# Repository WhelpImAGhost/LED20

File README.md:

# ECE 411 - LED20
### Team 1
- Brad Glaubitz
- Chris Kane-Pardy
- Caleb Monti
- Henry Sanders

## Project Overview
The purpose of the LED20 project is to add a fun and interesting spin to modern D20s (20 sided dice) for various tabletop games. Rather than a standard D20 which simply shows which face is rolled, the LED20 will illuminate the face that was rolled, and play special sound effects when a 1 or 20 is rolled. This added flare will spice up any tabletop game, and can be customized to your liking! [^1]

## Important Files and Folders Directory
This repository holds all design and development documents that were either assigned or created out of necessity throughout this project, including the Product Design Specification and Bill of Materials. However, for someone interested in creating their own copy of the LED20, some of these files and folders are not required. So, we have compiled a list of the files and folders that are necessary for understanding and replicating this project

### Links to files and folders
- [Full Project Description](./Project%20Info%20and%20Requirements/Project%20Information%20and%20Requirements.pdf): A more in-depth explanation of the project details and required features
- [Functional Decomposition](./Functional%20Decomposition/): Other high-detail files which explain the inner hardware and software functions and connections
- [Bill of Materials](./BOMs/Bill%20of%20Materials%20v4.xlsx): The list of required components to recreate the circuit
- [3D Model Files](./CAD/3D%20Model/): Iterations of development for the 3D printed D20 enclosure and charging base
- [PCB Development Files](./CAD/Schematics%20and%20PCB%20Layouts/): Required files for modifying or fabricating the carrier circuit board
- [Code](./LED20_Code/): Most recent iteration of the code, developed using ESP-IDF for the ESP32-C6

[^1]: Customization must take place before the die is sealed, as there is not a current way to interface with the processor after the enclosure is fully sealed. Please make any changes to LED Color, 1 & 20 Tones, and Sleep States before sealing your die.

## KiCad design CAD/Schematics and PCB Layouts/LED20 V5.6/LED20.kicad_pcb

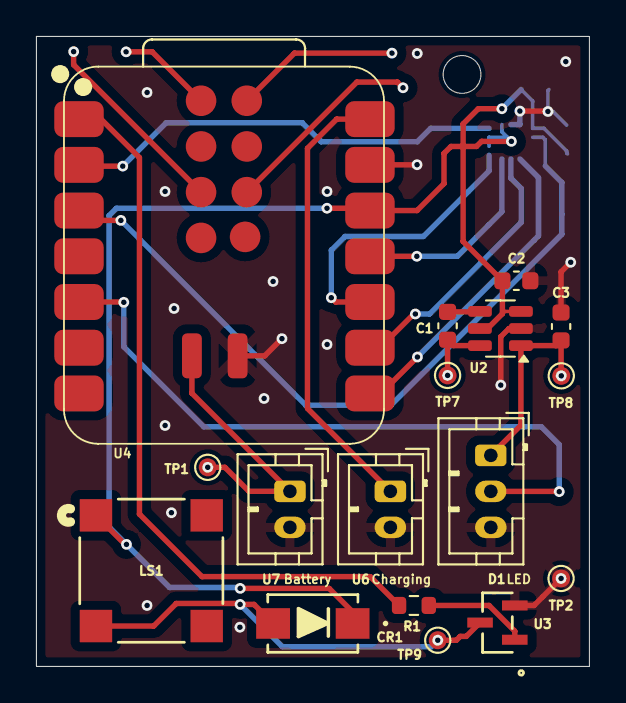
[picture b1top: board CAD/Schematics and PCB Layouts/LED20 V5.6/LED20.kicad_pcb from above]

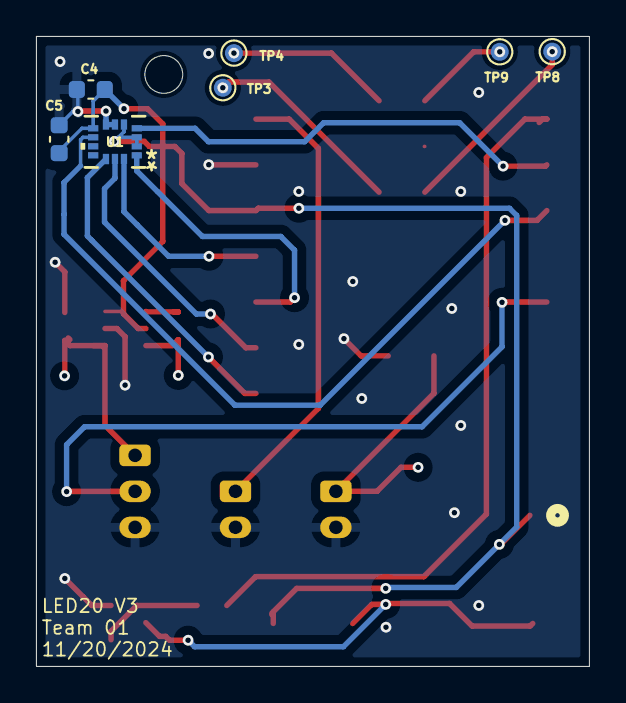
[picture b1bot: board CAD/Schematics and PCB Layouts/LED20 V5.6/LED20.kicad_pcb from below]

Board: 2 copper layers, 30.7 x 35.0 mm, 24 parts (7 on the bottom side), 17 nets.

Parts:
C1: 1u; C_0603_1608Metric
C2, C3: 10u; C_0603_1608Metric
C4, C5: 100n; C_0603_1608Metric
CR1: S1B; SMA_403AE_OSI
D1: SK6812MINI; JST_PH_B3B-PH-K_1x03_P2.00mm_Vertical
LS1: CMT-7525-80-SMT-TR; CMT-7525-80-SMT-TR_CUD
R1: 180; R_0603_1608Metric
TP1, TP2, TP3, TP4, TP5, TP6, TP7, TP8, TP9: TestPoint_Pad_D1.0mm
U1: LGA-14L_2P5X3X0P83_STM-L
U2: ChargePump
U3: MMBT4401LT1G; SOT-23_ONS
U4: XIAO-ESP32-C6-SMD
U6, U7: B2B-PH-K-S; JST_PH_B2B-PH-K_1x02_P2.00mm_Vertical

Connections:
3.3V: C2.1, C4.2, C5.2, CR1.1, LS1.1, U1.2 (SDx), U1.3 (SCx), U1.5 (VDDIO), U1.8 (VDD), U2.3 (!SHDN), U2.5 (VIN), U4.12 (3V3)
3.3V Data (D4): D1.2 (DIN), U4.5 (SDIO_DATA2/GPIO22/SDA/D4)
+5V: C3.2, D1.1 (VDD), TP8.1, U2.1 (5VO)
+5V IN: U4.14 (5V), U6.1
GND: C2.2, C3.1, C4.1, C5.1, D1.3 (VSS), TP2.1, U1.6 (GND), U1.7 (GND), U2.2 (GND), U3.2 (EMITTER), U4.13 (GND), U4.16 (-), U6.2, U7.2
unnamed: U1.12 (CS), U4.8 (GPIO17/RX/D7)
unnamed: U1.4 (INT1), U4.2 (LP_GPIO1/GPIO1/A1/D1)
unnamed: U1.9 (INT2), U4.3 (LP_GPIO2/GPIO2/A2/D2)
unnamed: U1.13 (SCL), U4.9 (SDIO_CLK/GPIO19/SCK/D8)
unnamed: U1.14 (SDA), U4.11 (SDIO_CMD/GPIO18/MOSI/D10)
unnamed: U1.1 (SDO/SA0), U4.10 (SDIO_DATA0/GPIO20/MISO/D9)
unnamed: C1.1, TP7.1, U2.6 (C+)
unnamed: C1.2, U2.4 (C-)
unnamed: R1.2, U3.1 (BASE)
unnamed: CR1.2, LS1.2, TP9.1, U3.3 (COLLECTOR)
unnamed: R1.1, U4.1 (LP_GPIO0/GPIO0/A0/D0)
VBATT: TP1.1, U4.15 (+), U7.1

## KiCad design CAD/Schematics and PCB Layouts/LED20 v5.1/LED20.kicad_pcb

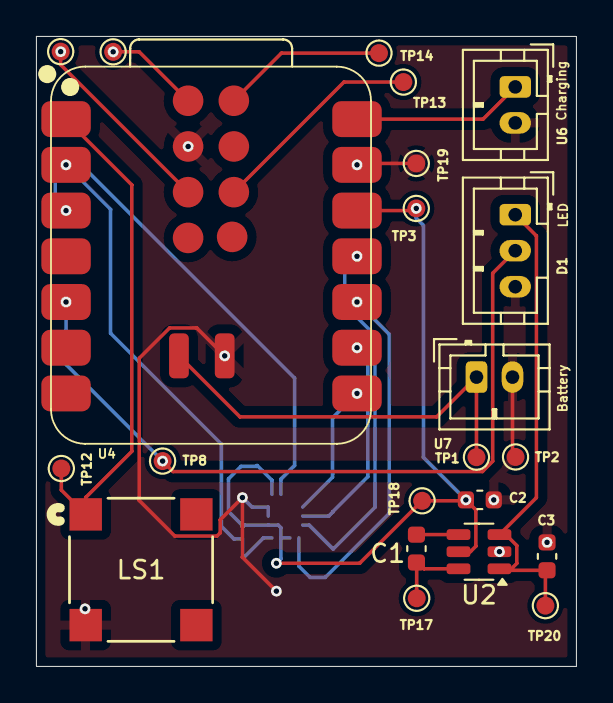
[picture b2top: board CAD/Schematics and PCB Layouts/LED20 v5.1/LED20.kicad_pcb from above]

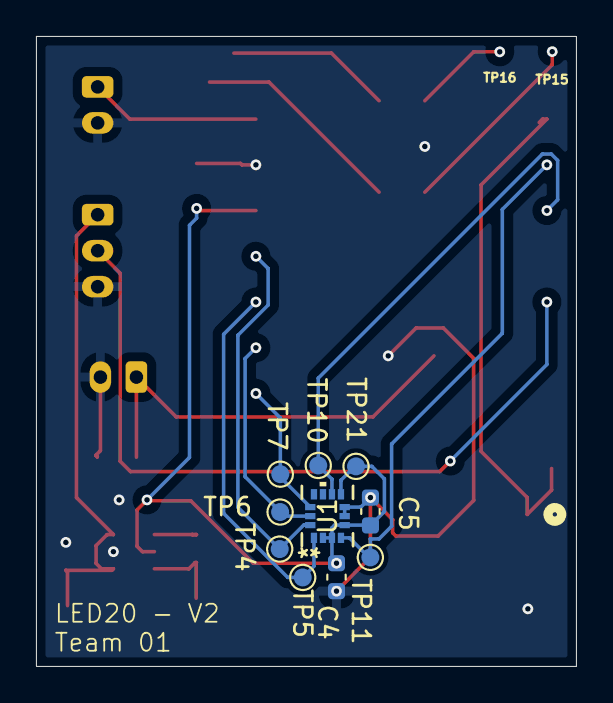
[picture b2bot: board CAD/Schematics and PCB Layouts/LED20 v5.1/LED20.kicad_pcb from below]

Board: 2 copper layers, 30.0 x 35.0 mm, 32 parts (10 on the bottom side), 15 nets.

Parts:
C1: 1u; C_0603_1608Metric
C2, C3: 10u; C_0603_1608Metric
C4, C5: 100n; C_0603_1608Metric
D1: SK6812MINI; JST_PH_B3B-PH-K_1x03_P2.00mm_Vertical
LS1: CMT-7525-80-SMT-TR; CMT-7525-80-SMT-TR_CUD
TP1, TP2, TP3, TP4, TP5, TP6, TP7, TP8, TP10, TP11, TP12, TP13, TP14, TP15, TP16, TP17, TP18, TP19, TP20, TP21: TestPoint_Pad_D1.0mm
U1: LGA-14L_2P5X3X0P83_STM-L
U2: ChargePump
U4: XIAO-ESP32-C6-SMD
U6, U7: B2B-PH-K-S; JST_PH_B2B-PH-K_1x02_P2.00mm_Vertical

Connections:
3.3V: C2.1, C4.2, C5.2, TP3.1, TP18.1, TP21.1, U1.2 (SDx), U1.3 (SCx), U1.5 (VDDIO), U1.8 (VDD), U2.5 (VIN), U4.12 (3V3)
3.3V Data (D4): D1.2 (DIN), TP8.1, U4.5 (SDIO_DATA2/GPIO22/SDA/D4)
+5V: C3.2, D1.1 (VDD), TP20.1, U2.1 (5VO), U2.3 (!SHDN)
+5V IN: U4.14 (5V), U6.1
GND: C2.2, C3.1, C4.1, C5.1, D1.3 (VSS), LS1.2, TP2.1, TP19.1, U1.6 (GND), U1.7 (GND), U2.2 (GND), U4.13 (GND), U4.16 (-), U4.19 (GND), U6.2, U7.2
unnamed: TP7.1, U1.12 (CS), U4.8 (GPIO17/RX/D7)
unnamed: TP11.1, U1.4 (INT1), U4.2 (LP_GPIO1/GPIO1/A1/D1)
unnamed: TP10.1, U1.9 (INT2), U4.3 (LP_GPIO2/GPIO2/A2/D2)
unnamed: TP6.1, U1.13 (SCL), U4.9 (SDIO_CLK/GPIO19/SCK/D8)
unnamed: TP4.1, U1.14 (SDA), U4.11 (SDIO_CMD/GPIO18/MOSI/D10)
unnamed: TP5.1, U1.1 (SDO/SA0), U4.10 (SDIO_DATA0/GPIO20/MISO/D9)
unnamed: C1.1, TP17.1, U2.6 (C+)
unnamed: C1.2, U2.4 (C-)
unnamed: LS1.1, TP12.1, U4.1 (LP_GPIO0/GPIO0/A0/D0)
VBATT: TP1.1, U4.15 (+), U7.1

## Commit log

2024-10-10 Organizing folder creations
    General template for where to add files
2024-10-10 Corrected Code and Documentation folders
2024-10-10 Update README.md
    Renamed repo as well as update readme
2024-10-10 Test webhook integration
2024-10-15 Added meeting notes and Project Ideas
2024-10-15 Added completed L0 and L1 block diagrams
2024-10-22 Testing setup for C6 programming. Testing only for now
2024-10-24 Test reconfigure .gitignore
2024-10-24 Test 2 of reconfiguration
2024-10-24 Test .gitignore part 3
2024-10-24 Final existing test of gitignore and basic code start
2024-10-26 Added schematic docs and PDS
2024-10-27 More basic testing and fun
    Don't ask why I am doing this at 2:30am after chugging an energy drink 2 hours ago
2024-10-28 Push current changes to Git for parallel coding
2024-10-29 fuck programming 1:29 AM -Chris & Caellb
2024-10-29 Revert "Push current changes to Git for parallel coding"
    This reverts commit 042efdc79f316fea88aa70c33bcac32e68842648.
2024-10-29 Revert "fuck programming 1:29 AM -Chris & Caellb"
    This reverts commit 249847f116f7c7f93000ef3a6b3220953b2464c3.
2024-10-29 Update gitignore
2024-10-29 update pt 2
2024-10-29 test
2024-10-29 final test?
2024-10-29 Holyshit it work
2024-10-29 Unbreak the code
2024-11-01 Big Git Commit
    Massive upload and rearrangement of most of our project files
2024-11-01 Create PDS Version 1.1.pdf
    Updated L0 and L1 block diagrams, added "wireless charging capabilities" to "May" requirements
2024-11-01 Updated to-do list
    PDS revision complete
    Gantt chart near complete
    Some other small edits
2024-11-01 Added Gantt Chart v1
    ~75% complete
    All class/project assignments added
    Still needs general project milestones, integration, testing, etc.
2024-11-01 Code update and added file for register explanation and values
2024-11-01 Start of info for setting up registers
2024-11-02 Functional large burst for Accel / Gyro burst reading
    Functional, but with a ~40ms delay between bursts of 12. I will look into other ways to reduce this delay, or see if the transactions need to happen anywhere near that speed.
2024-11-03 Added KiCAD symbols
    Added KiCAD symbols for ap3602, lsm6dso32, and xiao_esp32c6.
    Place in correct library
2024-11-03 Code works for sensing interrupts
    INT1 is for SMD, INT2 is for inactivity
2024-11-03 work from today
    Added custom footprint and digikey footprints
2024-11-05 Gantt Chart v2
    Made on Teamgantt
2024-11-05 Updated Schematic 11-4-24
    Removed Logic Level Shifter
    Added USB pins
    Added Test Points
    other various minor fixes
2024-11-05 Final revision of Updated Schematic 11-4-24
2024-11-05 PCB In Progress
    Progress for the PCB layout. Tracing and microcontroller footprint still needs to be done.
2024-11-05 Work on LED functionality
2024-11-05 Added Meeting Notes 11-4-24
2024-11-05 Led strip turned on once. More config to come
2024-11-05 Updated PCB
    Added esp32 footprint
2024-11-05 minor fixes
2024-11-06 Updated PCB
    Pins for Microcontroller on schematic had to be changed to reflect the footprint pin out. This may need closer attention for all ICs, i'll double check that tomorrow. Also found connector for battery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
2024-11-06 Updated PCB and Schematic
    Changed schematic to include charging contact points and double checked pinouts on ICs
2024-11-07 Updated PCB and Schematic
2024-11-07 Able to control every aspect of the project so far, and added breadboard prototype information
2024-11-07 dont worry bout it sweetheart
2024-11-07 one more time
2024-11-11 refined accel and gyro outputs for easier computation.
    I was bored and not very tired, but now my brain hurts :D
2024-11-12 Filtering set up, inactivity set up to trigger interrupt signal after ~10 seconds
2024-11-12 PCB and Schematic Update
2024-11-12 Added Functional Decomposition
2024-11-12 Added Meeting Notes 11/11
2024-11-12 PCB and Schematic Update
    Updated PCB with traces and ground planes. Needs review. Battery symbol for schematic was removed - JST connector remains in its place.
2024-11-12 Resubmit
    see previous notes
2024-11-12 Update to PCB
    Moved caps closer to ICs
2024-11-13 PCB Update and all kinds of stuff
2024-11-13 Update Directories
2024-11-14 Working interrupt detection and handling, switches between red and green when interrupts are detected while also outputting data
2024-11-14 Cleaned up slightly
2024-11-15 Working interrupt LED code
2024-11-16 Handful of Schemi/PCB directory edits
2024-11-16 Updated Directory and added new project contet
2024-11-16 More CAD directory changes
2024-11-16 moar
2024-11-16 Update PCB
    Updated test points, vias, and pcb traces. Added version number and team name to back of PCB.
2024-11-19 Added Meeting Notes 11-18
2024-11-19 Beautify logs and code, also interrupt functions work properly now
2024-11-20 PCB v5.2 local version WIP
    Moved connectors, accel/gyro, charge pump, retraced, etc.
    Added date to silkscreen
    Still needs ground stitching
    DRC yields handful of errors/warnings, needs review
2024-11-20 PCB and Schematic Update
    Updated PCB and Schematic with diode, transistor and resistor for piezo speaker driving circuit
2024-11-20 Ground plane update
2024-11-20 Updated PCB
    added 2.1mm mounting hole. Seems quite large may have clearance issues.
2024-11-21 Updated PCB
    Made new folder as well called v5.4 local, just in case we need v5.3
2024-11-21 (mostly) functional data parsing and averaging
2024-11-21 Proper data interpretation and sampling, no zero values
2024-11-21 Added design review
2024-11-21 We did it
2024-11-21 Eliminated redundant backups
2024-11-26 Face detection and specific-LED turning on works
2024-11-26 Heartbeat added
2024-12-03 Uploaded Test Plan
2024-12-05 Add buzzer and LED test functions
2024-12-05 Updated schematic and pcb layout to reflect charge pump !shdn connection change and fix esp32 footprint shenanigans
    LED v5.6
2024-12-05 Small revisions to final schematic, made pdf
2024-12-06 Full face detection working
2024-12-06 Fully functional other than LED sequence
2024-12-07 Added final Gantt Chart and Block Diagrams
2024-12-07 Final iteration of the code
2024-12-07 Why macos, why
2024-12-07 Deleted "Documentation" directory - unneeded
2024-12-09 Added images and basic README
2024-12-11 Rename Charger Testing (Maybe Final Version) v5.f3d to Charger Testing Final Version v5.f3d
2024-12-11 Rename LED20 Fat Ass Pegs (Updated) v3.f3d to LED20 Testing Pegs v3.f3d
2024-12-11 Updated BOM
2024-12-12 Update README.md
    fixed a typo
2024-12-12 Added PDS Version 1.2
